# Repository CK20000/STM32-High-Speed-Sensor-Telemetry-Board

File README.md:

# High-Speed Sensor Telemetry & Observer System Validation Board

## Project Overview
This repository contains the full hardware, firmware, and software stack for a custom sensor data acquisition board designed around the STM32F407VGT microcontroller. The system is engineered to capture, process, and stream multi-sensor data to validate a high-speed observer system framework. 

The architecture bridges custom PCB design, non-blocking C++ embedded firmware, and a modular Python dashboard to provide real-time telemetry, enabling precise tracking of stable motor rotation and load variables at high velocities.

---

## System Architecture

### 1. Hardware Integration (`/hardware`)
The custom-designed PCB acts as the central node for sensor fusion and motor state estimation. The board integrates the following components:
*   **MCU:** STM32F407VGT (ARM Cortex-M4).
*   **IMU:** MPU6050 (6-axis accelerometer and gyroscope) for inertial tracking.
*   **Magnetometer:** HMC5883L for heading reference.
*   **Time-of-Flight:** VL53L0X for precise distance measurements.
*   **Mechanical Sensors:** Direct interfaces for load cells and quadrature/optical encoders to track torque and rotation.
*   **Design Files:** KiCAD schematics, BOM, and mechanical CAD models are included.

### 2. Embedded Firmware (`/firmware`)
Written in C++, the firmware focuses on deterministic execution and high-speed data throughput:
*   **Non-Blocking I/O:** Ensures the sensor polling loop is not bottlenecked by communication delays.
*   **Telemetry Pipeline:** Constructs and streams an 84-byte binary payload containing timestamped sensor data and state variables.
*   **Virtual COM Port (VCP):** Utilizes USB CDC to achieve a stable 200Hz data transmission rate to the host PC. 

### 3. Telemetry Dashboard (`/software`)
A custom graphical interface developed in Python (PySide/PyQt) to visualize the observer system's performance in real-time.
*   **Serial Parsing (`comms.py`):** Efficiently unpacks the 84-byte binary stream at 200Hz.
*   **Real-Time Visualization (`gauges.py` / `ui/`):** Dynamic plotting of motor rotation, current readings, IMU data, and load metrics.
*   **Architecture:** Highly modular layout utilizing custom `.qss` stylesheets for a clean, industrial UI.

---

## Getting Started

### Prerequisites
*   **Hardware:** STM32 ST-LINK Utility or OpenOCD.
*   **Firmware:** ARM GCC Toolchain and CMake (or your preferred STM32 IDE like STM32CubeIDE).
*   **Software:** Python 3.8+ with `pyserial`, `PySide6` (or `PyQt6`), and `pyqtgraph`.

### Installation & Execution
1.  **Clone the Repository:**
    ```bash
    git clone [https://github.com/yourusername/stm32-telemetry-board.git](https://github.com/yourusername/stm32-telemetry-board.git)
    cd stm32-telemetry-board
    ```
2.  **Flash the Firmware:** 
    Compile the C++ source in the `/firmware` directory and flash the STM32F407 via ST-LINK.
3.  **Launch the Dashboard:**
    ```bash
    cd software
    pip install -r requirements.txt
    python main.py
    ```

---

## Current Development Status
*   [x] Custom PCB schematic and layout finalized.
*   [x] Virtual COM port pipeline validated (84-byte payload @ 200Hz).
*   [x] Python GUI rendering stable high-speed sensor plots.
*   [ ] Full observer system implementation in firmware (In Progress).

---

## License
This project is licensed under the MIT License - see the [LICENSE](LICENSE) file for details.

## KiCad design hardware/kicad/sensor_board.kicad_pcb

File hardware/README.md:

Contains the KiCAD schematic, PCB layouts, component bill of materials, and mechanical CAD files for the sensor board.

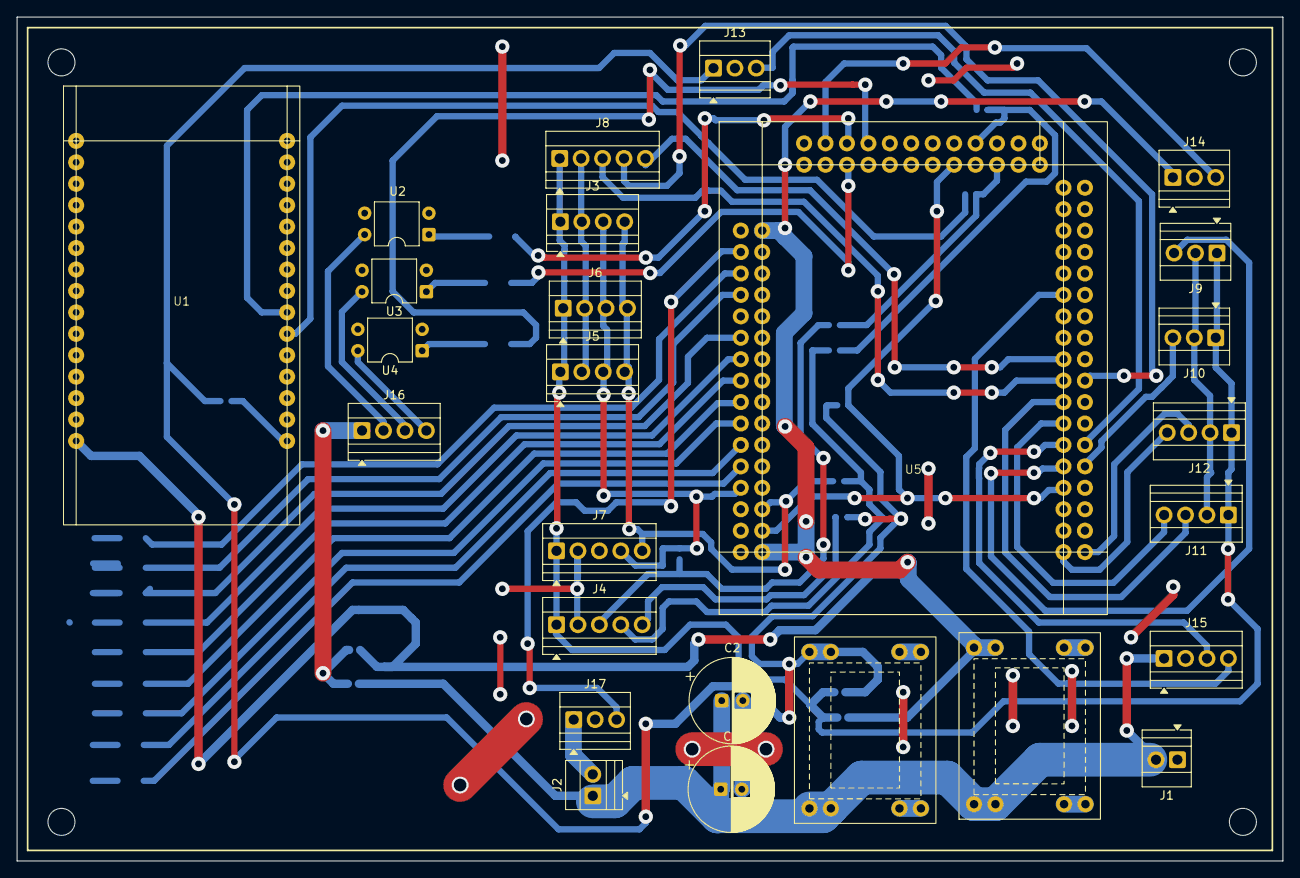
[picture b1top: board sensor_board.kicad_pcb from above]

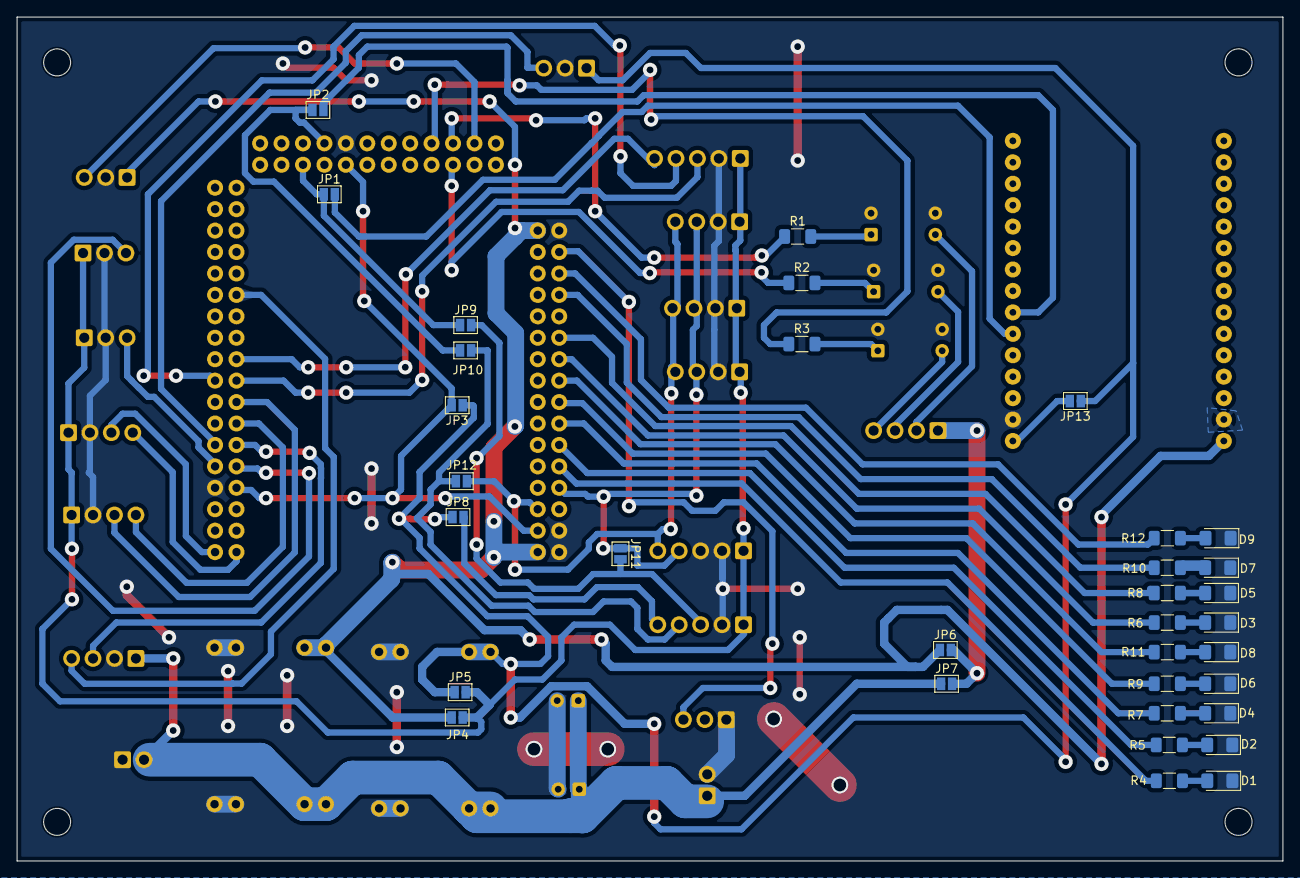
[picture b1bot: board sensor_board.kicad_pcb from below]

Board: 2 copper layers, 150.0 x 100.0 mm, 60 parts (34 on the bottom side), 58 nets.

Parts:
C1, C2: 470U; CP_Radial_D10.0mm_P2.50mm
D1, D2, D3, D4, D5, D6, D7, D8, D9: LED; LED_1206_3216Metric_Pad1.42x1.75mm_HandSolder
J1, J2: Screw_Terminal_01x02; TerminalBlock_Xinya_XY308-2.54-2P_1x02_P2.54mm_Horizontal
J3, J5, J6, J11, J12, J15, J16: Screw_Terminal_01x04; TerminalBlock_Xinya_XY308-2.54-4P_1x04_P2.54mm_Horizontal
J4, J7, J8: Screw_Terminal_01x05; TerminalBlock_Xinya_XY308-2.54-5P_1x05_P2.54mm_Horizontal
J9, J10, J13, J14, J17: Screw_Terminal_01x03; TerminalBlock_Xinya_XY308-2.54-3P_1x03_P2.54mm_Horizontal
JP1, JP2, JP3, JP4, JP5, JP6, JP7, JP8, JP9, JP10, JP11, JP12, JP13: SolderJumper_2_Open; SolderJumper-2_P1.3mm_Open_Pad1.0x1.5mm
MP1_5, MP2_3.3: MP1584
R1, R2, R3, R4, R5, R6, R7, R8, R9, R10, R11, R12: 330; R_1206_3216Metric_Pad1.30x1.75mm_HandSolder
U1: ESP32_WROOM_32
U2, U3, U4: Optocoupler_DC_PhotoNPN_AKEC; DIP-4_W7.62mm
U5: STM32_F407VGT

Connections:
+12V: C1.1, C2.1, J1.2, J2.1, J15.1, JP7.1 (A), MP1_5.1 (Vin), MP1_5.2, MP2_3.3.1 (Vin), MP2_3.3.2
/3v3: J13.1, JP3.1 (A), JP5.1 (A), JP8.1 (A), JP13.1 (A), MP2_3.3.5 (Vout), MP2_3.3.6
/5v: J14.1, JP4.1 (A), JP6.1 (A), MP1_5.5 (Vout), MP1_5.6, U1.15 (VCC), U5.2 (VCC), U5.32 (VCC)
GND: C1.2, C2.2, D1.1 (K), D2.1 (K), D3.1 (K), D4.1 (K), D5.1 (K), D6.1 (K), D7.1 (K), D8.1 (K), D9.1 (K), J1.1, J2.2, J3.2, J4.2, J5.2, J6.2, J7.2, J7.3, J8.2, J9.2, J10.2, J11.2, J12.2, J13.2, J14.2, J15.2, J17.1, MP1_5.3, MP1_5.4 (GND), MP1_5.7, MP1_5.8 (GND), MP2_3.3.3, MP2_3.3.4 (GND), MP2_3.3.7, MP2_3.3.8 (GND), U1.14 (GND), U1.17 (GND), U2.2, U2.3, U3.2, U3.3, U4.2, U4.3, U5.1 (GND), U5.29 (GND), U5.31 (GND), U5.62 (GND), U5.83 (GND)
unnamed: D1.2 (A), R4.2
unnamed: D2.2 (A), R5.2
unnamed: D3.2 (A), R6.2
unnamed: D4.2 (A), R7.2
unnamed: D5.2 (A), R8.2
unnamed: D6.2 (A), R9.2
unnamed: D7.2 (A), R10.2
unnamed: D8.2 (A), R11.2
unnamed: D9.2 (A), R12.2
unnamed: J3.3, J5.3, J6.3, J7.4, JP11.1 (A), U5.25 (PB6)
unnamed: J3.4, J5.4, J6.4, J7.5, JP12.1 (A), U5.28 (PB7)
unnamed: J4.3, JP9.2 (B), JP11.2 (B)
unnamed: J4.4, JP10.2 (B), JP12.2 (B)
unnamed: J4.5, JP8.2 (B)
unnamed: J8.3, U5.51 (PA4)
unnamed: J8.4, U5.52 (PA5)
unnamed: J8.5, U5.49 (PA6)
unnamed: J9.3, U5.59 (PC0)
unnamed: J3.1, J4.1, J5.1, J6.1, J7.1, J8.1, J9.1, J10.1, J11.1, J12.1, JP4.2 (B), JP5.2 (B)
unnamed: J10.3, U5.60 (PC1)
unnamed: J11.3, U5.53 (PA3)
unnamed: J11.4, U5.55 (PA2)
unnamed: J12.3, U5.68 (PE3)
unnamed: J12.4, U5.67 (PE2)
unnamed: J13.3, U5.58 (PA0)
unnamed: J14.3, U5.71 (PC6)
unnamed: J15.3, U5.57 (PC2)
unnamed: J15.4, U5.43 (PB8)
unnamed: J16.1, JP6.2 (B), JP7.2 (B)
unnamed: J16.2, U2.4
unnamed: J16.3, U3.4
unnamed: J16.4, U4.4
unnamed: J17.3, U5.3 (PA8)
unnamed: JP1.1 (A), JP9.1 (A), U5.88 (PB10)
unnamed: JP1.2 (B), U1.21 (RX)
unnamed: JP2.2 (B), U1.22 (TX)
unnamed: JP3.2 (B), U5.30 (3V3), U5.61 (3V3), U5.84 (3V3)
unnamed: JP2.1 (A), JP10.1 (A), U5.85 (PB11)
unnamed: JP13.2 (B), U1.16 (3V3)
unnamed: R1.2, U2.1
unnamed: R2.2, U3.1
unnamed: R3.2, U4.1
unnamed: R12.1, U5.5 (PA10)
unnamed: R10.1, U5.7 (PA12)
unnamed: R4.1, U5.23 (PB4)
unnamed: R8.1, U5.11 (PC10)
unnamed: R6.1, U5.13 (PC12)
unnamed: R11.1, U5.15 (PD1)
unnamed: R9.1, U5.17 (PD3)
unnamed: R7.1, U5.19 (PD5)
unnamed: R5.1, U5.21 (PD7)
unnamed: R3.1, U5.75 (PD12)
unnamed: R2.1, U5.74 (PD13)
unnamed: R1.1, U5.73 (PD14)
